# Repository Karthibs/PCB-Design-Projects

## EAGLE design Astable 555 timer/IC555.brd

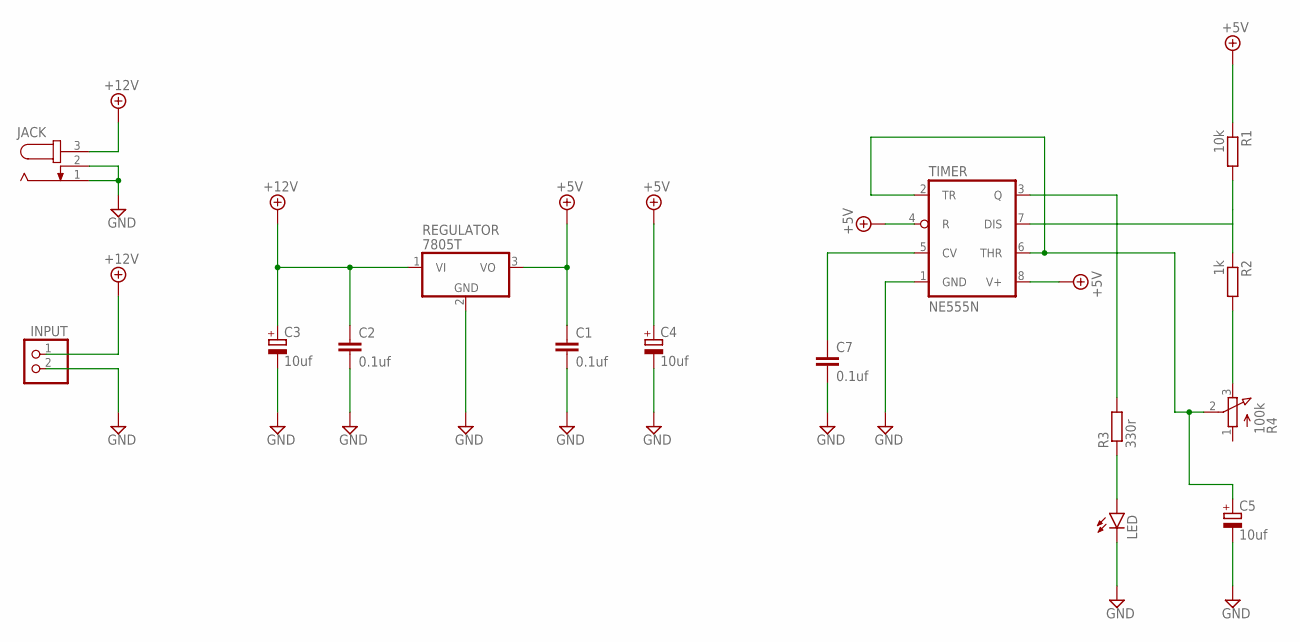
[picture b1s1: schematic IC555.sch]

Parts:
C1, C2, C7: 0.1uf; C050-030X075
C3, C4, C5: 10uf; E3,5-8
INPUT: PINHD-1X2; 1X02
JACK: JACK-PLUG0; SPC4077
LED: LED5MM
R1: 10k; 0207/10
R2: 1k; 0207/10
R3: 330r; 0207/10
R4: 100k; 3RP/1610N
REGULATOR: 7805T; TO220H
TIMER: NE555N; DIL08

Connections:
+5V: C1.1, C4.+, R1.1, REGULATOR.3 (VO), TIMER.4 (R), TIMER.8 (V+)
+12V: C2.1, C3.+, INPUT.1, JACK.3, REGULATOR.1 (VI)
GND: C1.2, C2.2, C3.-, C4.-, C5.-, C7.2, INPUT.2, JACK.1, JACK.2, LED.K (C), REGULATOR.2 (GND), TIMER.1 (GND)
unnamed: C7.1, TIMER.5 (CV)
unnamed: R3.2, TIMER.3 (Q)
unnamed: LED.A, R3.1
unnamed: R1.2, R2.1, TIMER.7 (DIS)
unnamed: R2.2, R4.3 (E)
unnamed: C5.+, R4.2 (S), TIMER.2 (TR), TIMER.6 (THR)

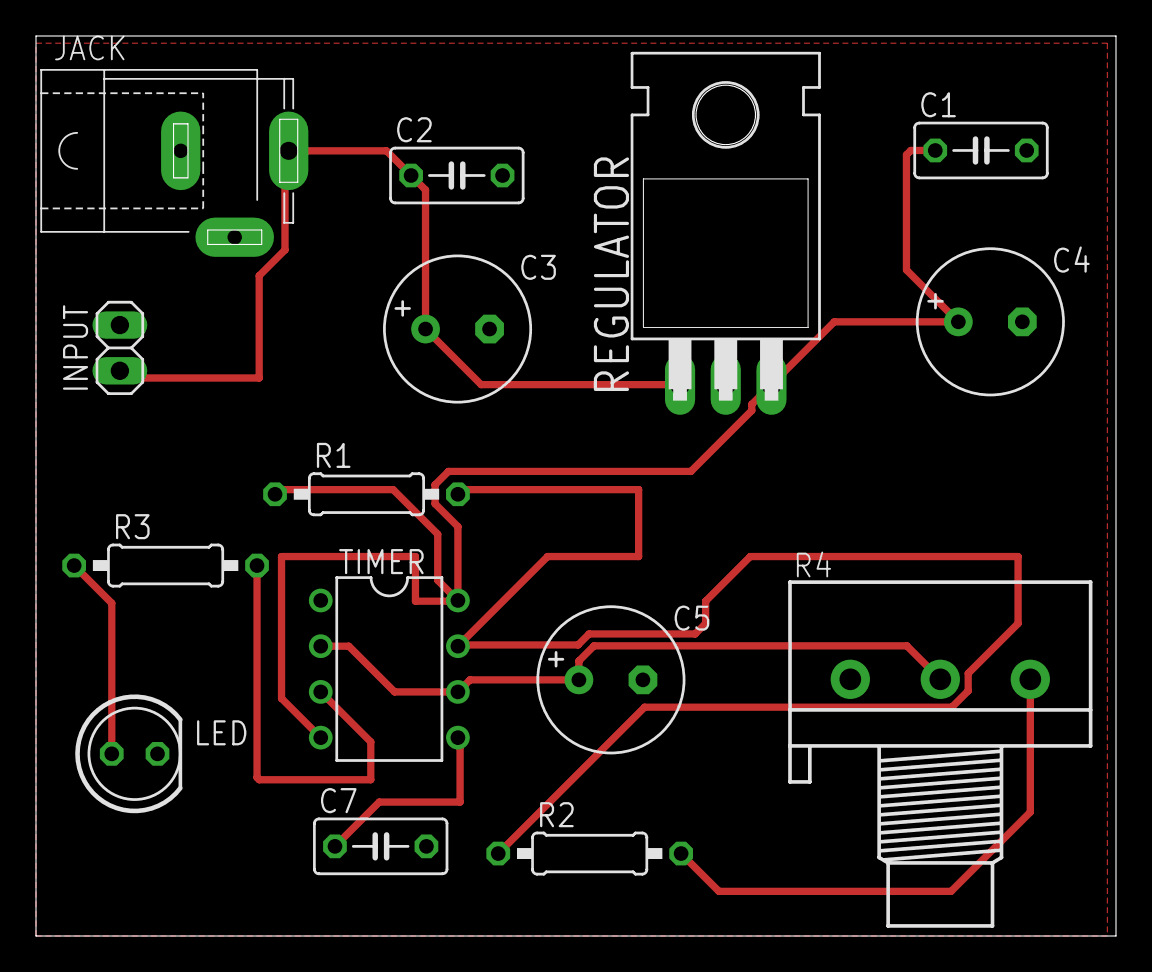
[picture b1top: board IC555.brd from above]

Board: 2 copper layers, 60.0 x 50.0 mm, 15 parts (0 on the bottom side), 9 nets.

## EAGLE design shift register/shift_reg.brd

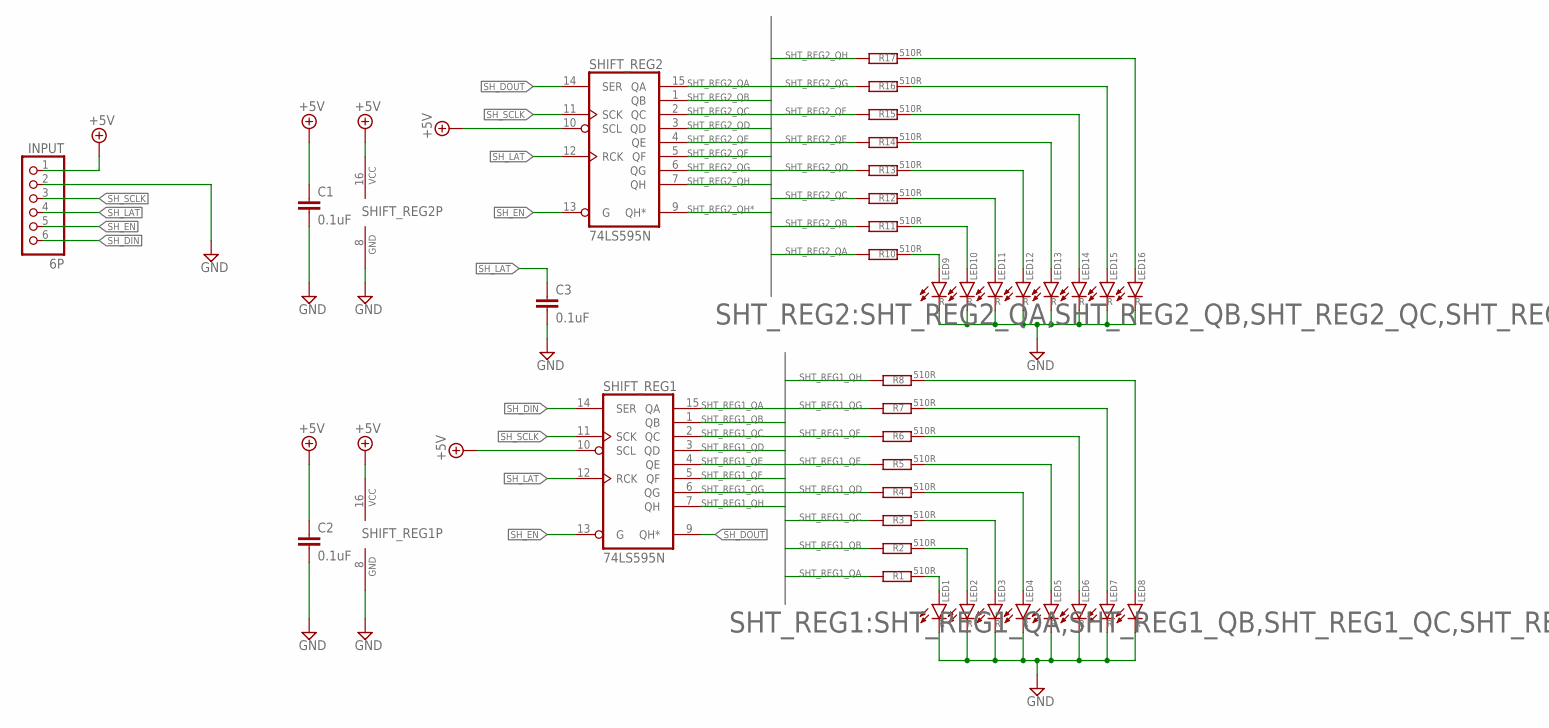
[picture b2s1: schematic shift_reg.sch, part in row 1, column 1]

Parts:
C1, C2, C3: 0.1uF; C050-030X075
INPUT: 6P; 1X06/90
LED1, LED2, LED3, LED4, LED5, LED6, LED7, LED8, LED9, LED10, LED11, LED12, LED13, LED14, LED15, LED16: R; LED5MM
R1, R2, R3, R4, R5, R6, R7, R8, R10, R11, R12, R13, R14, R15, R16, R17: 510R; 0207/10
SHIFT_REG1, SHIFT_REG2: 74LS595N; DIL16

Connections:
+5V: C1.1, C2.1, INPUT.1, SHIFT_REG1.10 (SCL), SHIFT_REG1.16 (VCC), SHIFT_REG2.10 (SCL), SHIFT_REG2.16 (VCC)
GND: C1.2, C2.2, C3.2, INPUT.2, LED1.K (C), LED2.K (C), LED3.K (C), LED4.K (C), LED5.K (C), LED6.K (C), LED7.K (C), LED8.K (C), LED9.K (C), LED10.K (C), LED11.K (C), LED12.K (C), LED13.K (C), LED14.K (C), LED15.K (C), LED16.K (C), SHIFT_REG1.8 (GND), SHIFT_REG2.8 (GND)
unnamed: LED1.A, R1.2
unnamed: LED2.A, R2.2
unnamed: LED3.A, R3.2
unnamed: LED4.A, R4.2
unnamed: LED5.A, R5.2
unnamed: LED6.A, R6.2
unnamed: LED7.A, R7.2
unnamed: LED8.A, R8.2
unnamed: LED9.A, R10.2
unnamed: LED10.A, R11.2
unnamed: LED11.A, R12.2
unnamed: LED12.A, R13.2
unnamed: LED13.A, R14.2
unnamed: LED14.A, R15.2
unnamed: LED15.A, R16.2
unnamed: LED16.A, R17.2
SHT_REG1_QA: R1.1, SHIFT_REG1.15 (QA)
SHT_REG1_QB: R2.1, SHIFT_REG1.1 (QB)
SHT_REG1_QC: R3.1, SHIFT_REG1.2 (QC)
SHT_REG1_QD: R4.1, SHIFT_REG1.3 (QD)
SHT_REG1_QE: R5.1, SHIFT_REG1.4 (QE)
SHT_REG1_QF: R6.1, SHIFT_REG1.5 (QF)
SHT_REG1_QG: R7.1, SHIFT_REG1.6 (QG)
SHT_REG1_QH: R8.1, SHIFT_REG1.7 (QH)
SHT_REG2_QA: R10.1, SHIFT_REG2.15 (QA)
SHT_REG2_QB: R11.1, SHIFT_REG2.1 (QB)
SHT_REG2_QC: R12.1, SHIFT_REG2.2 (QC)
SHT_REG2_QD: R13.1, SHIFT_REG2.3 (QD)
SHT_REG2_QE: R14.1, SHIFT_REG2.4 (QE)
SHT_REG2_QF: R15.1, SHIFT_REG2.5 (QF)
SHT_REG2_QG: R16.1, SHIFT_REG2.6 (QG)
SHT_REG2_QH: R17.1, SHIFT_REG2.7 (QH)
SHT_REG2_QH*: SHIFT_REG2.9 (QH*)
SH_DIN: INPUT.6, SHIFT_REG1.14 (SER)
SH_DOUT: SHIFT_REG1.9 (QH*), SHIFT_REG2.14 (SER)
SH_EN: INPUT.5, SHIFT_REG1.13 (G), SHIFT_REG2.13 (G)
SH_LAT: C3.1, INPUT.4, SHIFT_REG1.12 (RCK), SHIFT_REG2.12 (RCK)
SH_SCLK: INPUT.3, SHIFT_REG1.11 (SCK), SHIFT_REG2.11 (SCK)

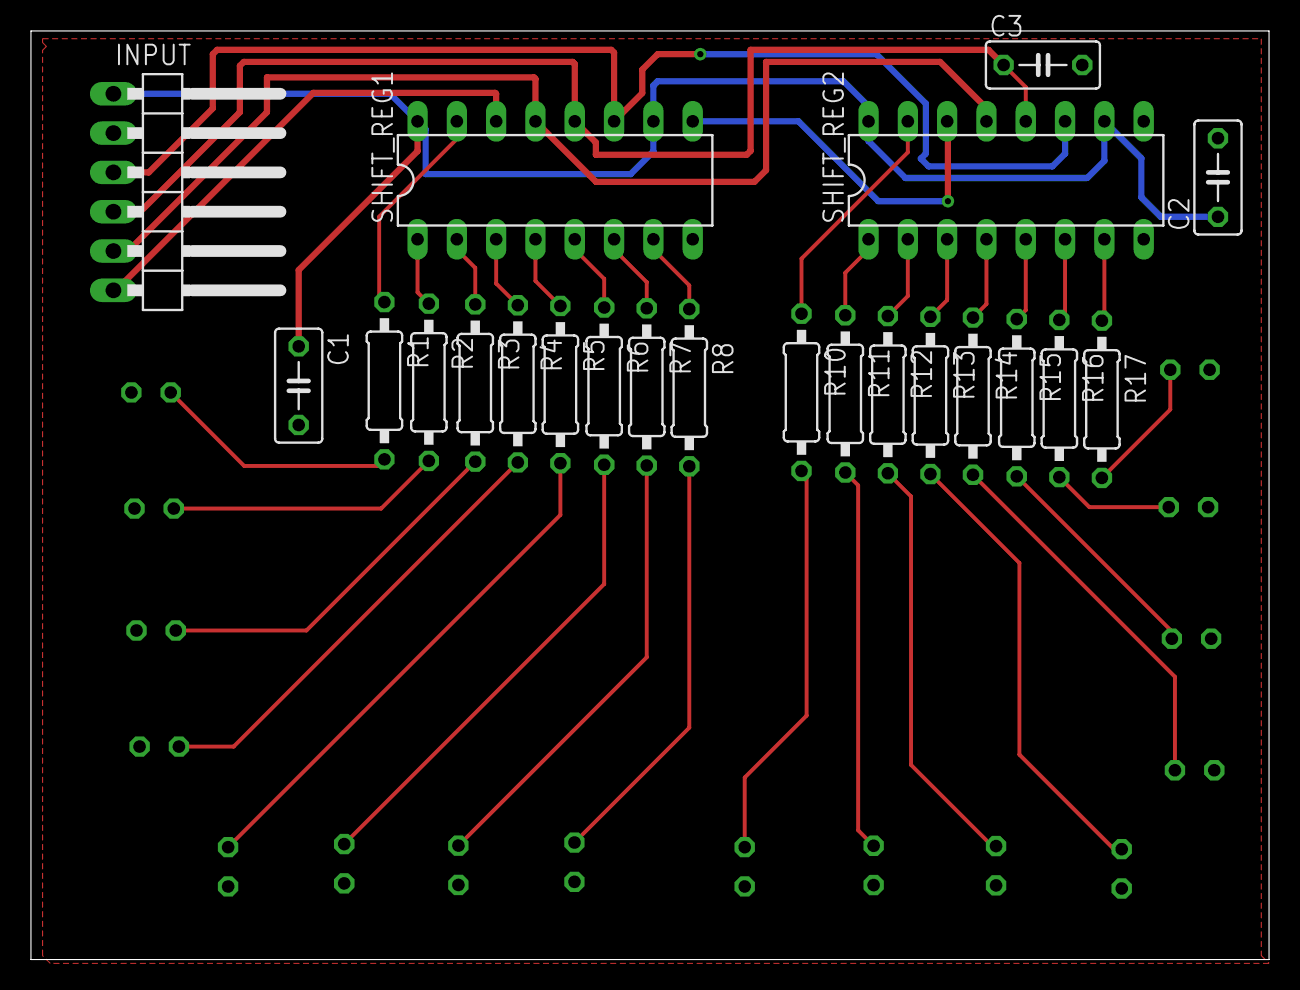
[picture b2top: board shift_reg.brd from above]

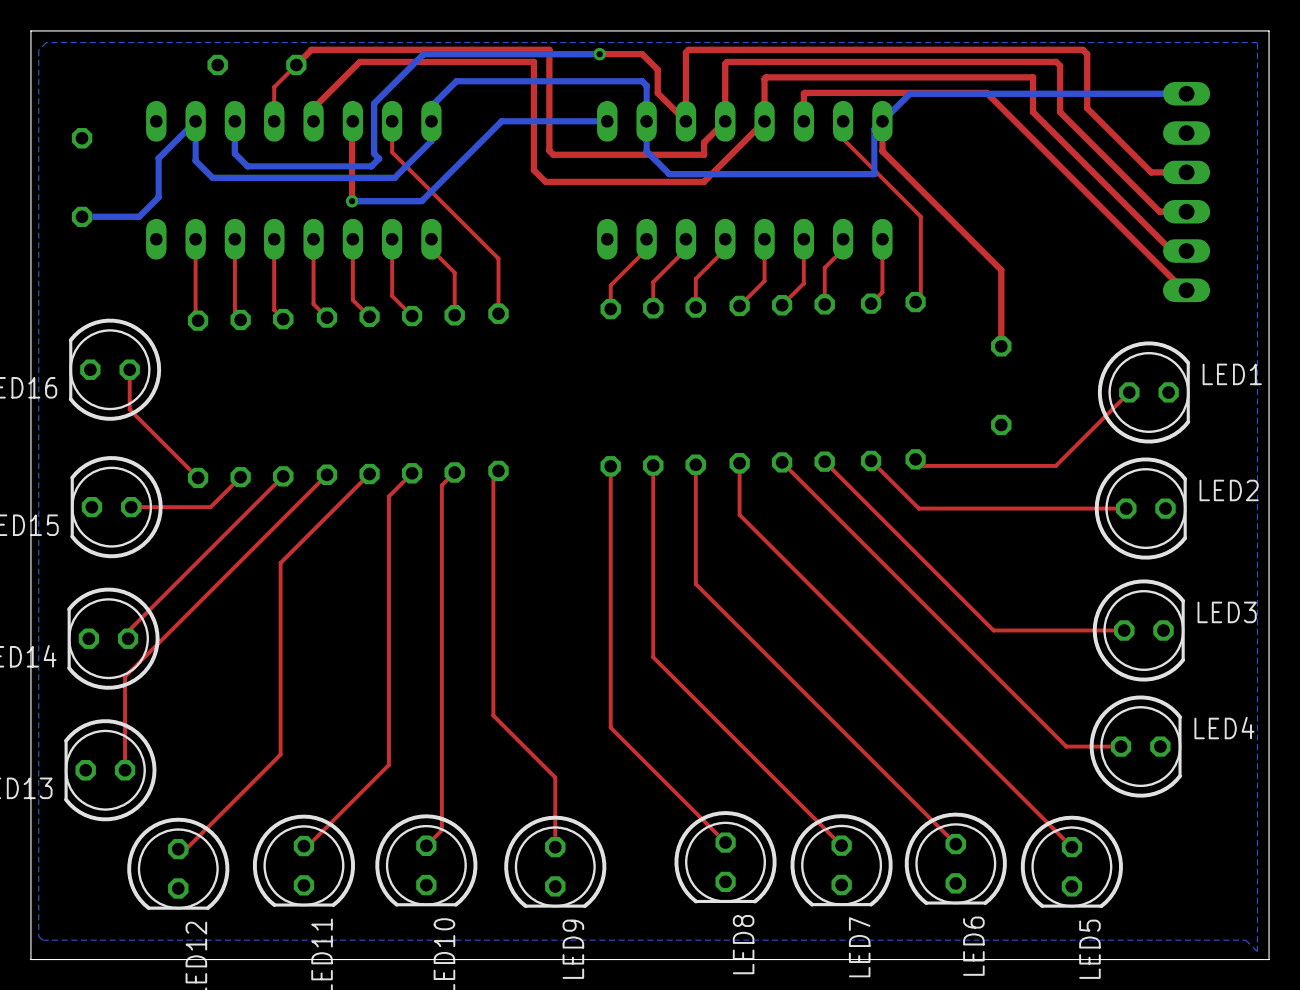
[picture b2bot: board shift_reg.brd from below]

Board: 2 copper layers, 80.0 x 60.0 mm, 38 parts (16 on the bottom side), 39 nets.
